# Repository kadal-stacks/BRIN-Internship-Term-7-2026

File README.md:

<!-- Official BRIN logo sourced from Wikimedia Commons; no AI-generated imagery is used. -->
<p align="center">
  
</p>

<h1 align="center">BRIN Internship | Term 7 · 2026</h1>

<p align="center">
  Catatan kerja dan hasil praktik di bidang embedded systems, firmware mikrokontroler, serta desain rangkaian dan PCB.
</p>

<p align="center">

</p>

---

## Tentang repositori

Repositori ini mengumpulkan pekerjaan teknis selama **Magang BRIN Term 7 (2026)**. Isinya berkembang melalui proyek KiCad untuk perancangan elektronik dan PCB, eksperimen program mikrokontroler, serta contoh firmware untuk latihan dan pengujian.

Struktur dibuat mengikuti kelompok pekerjaan agar file desain, source code, dan library pendukung tetap berada dekat dengan proyek masing-masing. Status setiap desain perlu dinilai dari file dan hasil verifikasi yang tersedia; keberadaan file proyek tidak otomatis berarti desain sudah tervalidasi atau siap fabrikasi.

## Ruang lingkup

### 1. Desain elektronik dan PCB dengan KiCad

| Folder | Isi |
| --- | --- |
| [`KiCAD/ATMega16-STM32 BP Adapter`](KiCAD/ATMega16-STM32%20BP%20Adapter) | Proyek adapter/pemetaan koneksi ATmega16 ke board STM32, dengan varian **SMD** dan **THT**. Berisi project, schematic, layout PCB, dan file pendukung yang tersedia. |
| [`KiCAD/Howland-VCCS`](KiCAD/Howland-VCCS) | Proyek rangkaian Howland Voltage-Controlled Current Source menggunakan TL072, dengan beberapa varian footprint/perakitan. |
| [`KiCAD/Impedance-meter2D_Main Board`](KiCAD/Impedance-meter2D_Main%20Board) | Folder proyek untuk main board impedance meter. Kelengkapan desain dapat berbeda dari proyek lainnya. |
| [`KiCAD/Part Lib/Kicad-STM32`](KiCAD/Part%20Lib/Kicad-STM32) | Library simbol, footprint, dan model 3D untuk modul STM32 **Blue Pill** dan **Black Pill**. Lihat README di dalam folder untuk rincian library. |
| [`KiCAD/Folder Tugas`](KiCAD/Folder%20Tugas) | Folder untuk materi/tugas KiCad. |

Format yang umum dijumpai antara lain `.kicad_pro` (project), `.kicad_sch` (schematic), `.kicad_pcb` (PCB layout), `.kicad_sym` (symbol library), dan `.kicad_mod` (footprint).

### 2. Firmware dan eksperimen mikrokontroler

| Lokasi | Isi |
| --- | --- |
| [`Program_MCU/AVR/AVR Atmega 328p - Arduino UNO R3`](Program_MCU/AVR/AVR%20Atmega%20328p%20-%20Arduino%20UNO%20R3) | Eksperimen pada ATmega328P/Arduino Uno R3, termasuk proyek ADC dan program LED non-blocking. |
| [`LED-Berjalan.cpp`](LED-Berjalan.cpp) | Contoh program LED berjalan. |
| [`Non-blocking using Multi LED.cpp`](Non-blocking%20using%20Multi%20LED.cpp) | Contoh pengaturan beberapa pola LED tanpa bergantung pada jeda blocking di loop utama. |

Sebagian proyek firmware memiliki `platformio.ini` dan dapat dibuka sebagai proyek PlatformIO. Untuk source code yang berdiri sendiri, pilih board, framework, pin, serta konfigurasi build yang sesuai sebelum mengompilasi.

## Deliverable PCB dan firmware terbaru

### PCB dengan paket Gerber dan gambar area

| Board | Luas outline | Dokumentasi |
| --- | ---: | --- |
| ATmega16–STM32 Adapter SMD | 1,450.75 mm² (14.5075 cm²) | [Gerber, drill, dan gambar area](KiCAD/ATMega16-STM32%20BP%20Adapter/ATMega16-STM32%20BP%20Adapter_SMD/README.md) |
| Howland VCCS TL072 THT | 3,506.24 mm² (35.0624 cm²) | [Gerber, drill, dan gambar area](KiCAD/Howland-VCCS/Howland-VCCS-TL072/README.md) |
| Howland VCCS TL072 SMD/hybrid | 618.85 mm² (6.1885 cm²) | [Gerber, drill, dan gambar area](KiCAD/Howland-VCCS/Howland-VCCS-TL072_SMD/Howland-VCCS-TL072_SMD/README.md) |

Luas dihitung dari outline `Edge.Cuts` pada file PCB sebagai rounded rectangle, bukan dari perkiraan visual. Board Raspberry Pi Zero Dev Board juga memiliki ukuran outline yang didokumentasikan, tetapi Gerber belum tersedia.

### Firmware AD9833

- [VCCS–AD9833 Frequency Controller (Arduino Nano)](Program_MCU/AVR/AVR%20Atmega%20328p%20-%20Arduino%20Nano/VCCS-AD9833%20Regulator/README.md)
- [Salinan di folder Arduino UNO R3](Program_MCU/AVR/AVR%20Atmega%20328p%20-%20Arduino%20UNO%20R3/VCCS%20-%20AD9833%20Regulator/README.md). Catatan: konfigurasi `platformio.ini` saat ini masih memilih board Nano.

## Alur kerja

Alur berikut merangkum cara menavigasi dan melanjutkan pekerjaan di repositori ini. Langkah verifikasi tetap perlu disesuaikan dengan proyek dan hardware yang digunakan.

1. **Pilih proyek yang relevan.** Buka folder di `KiCAD/` untuk pekerjaan desain atau `Program_MCU/` untuk eksperimen firmware.
2. **Buka file proyek utama.** Untuk KiCad, buka file `.kicad_pro` di folder proyek agar hubungan schematic, PCB, dan library lokal lebih mudah dipertahankan.
3. **Periksa keterkaitan desain.** Pastikan nomor pin, nama net, simbol, footprint, orientasi konektor, ukuran mekanik, dan tegangan logika sesuai datasheet serta modul fisik. Hal ini sangat penting untuk adapter ATmega16–STM32.
4. **Verifikasi sebelum menganggap selesai.** Tinjau Electrical Rules Checker (ERC) untuk schematic dan Design Rules Checker (DRC) untuk PCB. Periksa hasil simulasi atau pengujian firmware jika tersedia. ERC/DRC yang bersih sendiri tidak menjamin rangkaian bekerja pada hardware.
5. **Simpan perubahan secara terstruktur.** Pertahankan file yang dibutuhkan proyek, hindari memasukkan file lock atau file sementara editor, lalu commit perubahan dengan pesan yang menjelaskan lingkup pekerjaan.

## Referensi visual

Gambar di bawah merupakan tangkapan layar asli dari dokumentasi KiCad, digunakan sebagai referensi antarmuka schematic dan PCB editor, bukan sebagai klaim bahwa gambar tersebut adalah hasil desain proyek ini.

<p align="center">

</p>

## Galeri perangkat keras: foto referensi non-AI

Foto berikut berasal dari halaman produk/vendor atau aset foto yang sudah tersimpan di repository. Gambar membantu mengenali komponen, **bukan bukti bahwa board pada proyek ini sudah dirakit atau diuji**.

<p align="center">

</p>

<sub>Sumber foto: <a href="https://www.mikroe.com/atmega16">MikroE ATmega16</a>, aset <a href="KiCAD/Part%20Lib/Kicad-STM32/README.md">Blue Pill repository</a>, <a href="https://www.ti.com/product/TL072">TI TL072 / foto paket IC dari pemasok</a>, <a href="https://wholesale.pimoroni.com/en-eu/products/adafruit-bmp280-i2c-or-spi-barometric-pressure-altitude-sensor">modul BMP280 dari pemasok</a>, dan <a href="https://laelectronica.com.gt/arduino-uno-rev3">foto Arduino Uno R3</a>. Foto TL072 yang ditampilkan adalah paket DIP-8; periksa footprint proyek sebelum membeli komponen.</sub>

## Memulai

- **KiCad:** instal KiCad, lalu buka file `.kicad_pro` dari folder proyek yang akan dikerjakan.
- **Firmware:** untuk proyek yang memiliki `platformio.ini`, gunakan VS Code dengan ekstensi PlatformIO atau PlatformIO CLI. Pastikan board/framework cocok dengan konfigurasi proyek.
- **Hardware:** sebelum upload firmware atau memberi daya, cocokkan wiring dan level tegangan dengan datasheet serta lakukan pemeriksaan dasar untuk menghindari kerusakan komponen.

## Catatan status dan akurasi

Repositori ini merupakan arsip kerja yang berkembang. Skema, mapping pin, footprint, routing, pengaturan panel, dan source code perlu diverifikasi terhadap versi tool, datasheet komponen, hardware aktual, serta persyaratan manufaktur. Jangan menganggap desain siap produksi hanya berdasarkan visual layout atau status file yang sudah di-commit.

## Sumber gambar dan aset

- **Logo BRIN:** karya resmi Badan Riset dan Inovasi Nasional; ditautkan dari [Wikimedia Commons](https://commons.wikimedia.org/wiki/File:LOGO_BRIN_NEW.jpg), yang mencatat sumber dan status domain publik di Indonesia.
- **Tangkapan layar KiCad:** [KiCad 8 release article](https://www.kicad.org/blog/2024/02/Version-8.0.0-Released/) dan [dokumentasi PCB Editor KiCad](https://docs.kicad.org/9.0/it/pcbnew/pcbnew.html).
- **Library STM32:** lihat [README library lokal](KiCAD/Part%20Lib/Kicad-STM32/README.md) untuk detail simbol, footprint, model 3D, dan konteks sumbernya.

<p align="center">
  <sub>Logo BRIN digunakan untuk menunjukkan konteks kegiatan magang. Repositori ini tidak menyatakan dirinya sebagai repositori resmi BRIN.</sub>
</p>

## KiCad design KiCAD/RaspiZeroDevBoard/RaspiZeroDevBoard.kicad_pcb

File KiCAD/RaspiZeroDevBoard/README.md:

<p align="center">
  
</p>

# Raspberry Pi Zero Dev Board

Carrier/development board untuk Raspberry Pi Zero dengan interface tambahan untuk akuisisi analog, komunikasi, RTC, display, dan distribusi daya.

## Preview area board

| Parameter | Nilai |
| --- | ---: |
| Lebar outline | 120.65 mm |
| Tinggi outline | 162.56 mm |
| Radius sudut | 6 mm |
| Luas bounding rectangle | 19,612.86 mm² |
| Koreksi empat sudut rounded | 30.90 mm² |
| **Luas bidang PCB aktual** | **19,581.96 mm²** |
| **Konversi** | **195.8196 cm²** |

Luas dihitung dari rounded-rectangle pada layer `Edge.Cuts` file `RaspiZeroDevBoard.kicad_pcb`:

`A = W × H − (4 − π)r²`

SVG adalah gambar ukur/preview vektor yang dibuat dari geometri CAD. Ini bukan foto produk, bukan render AI, dan bukan plot Gerber.

## Fungsi board

Schematic menunjukkan carrier board Raspberry Pi Zero dengan sejumlah interface eksternal:

| Blok | Komponen/label pada schematic | Fungsi yang dituju |
| --- | --- | --- |
| Host | J1, footprint Raspberry Pi Zero socketed | Koneksi modul Raspberry Pi Zero |
| ADC | U2 ADS1115, input ADC_Input0–ADC_Input3, R/C bertanda ADC_R/ADC_C | Empat kanal input analog melalui ADC eksternal |
| RTC | A2, Module_ZS-042 | Modul RTC DS3231 |
| RS-485 | U1, TLL_TO_RS-485 / module MAX485 | Interface komunikasi RS-485 |
| Display | A1, I2C-LCD1602 | Display karakter 16×2 melalui I²C |
| DC-DC | PS1, LM2596_Module | Modul regulator DC-DC |
| Serial/peripheral | Header UART, SPI, I²C | Akses interface peripheral |
| Power | Power_In, 5V Out, 3V3 Out | Input dan distribusi rail daya |
| User I/O | Tombol SW1/SW2, LED D1/D2, solder jumper | Kontrol lokal, indikator, dan konfigurasi board |

Schematic juga menunjukkan solder-jumper untuk pemilihan alamat ADS1115 (0x49, 0x4A, 0x4B), enable LED, enable button, RTC interrupt/SQW, dan arah RS-485. Nilai komponen bertanda generik seperti `ADC_R`, `ADC_C`, `I2C_R`, dan `R_LED` perlu diselesaikan pada BOM sebelum produksi.

## Catatan desain yang perlu diverifikasi

- Symbol J1 bernilai `Raspberry_Pi_4`, sedangkan footprint-nya bernama Raspberry Pi Zero. Pastikan symbol/value hanya label yang belum diperbarui atau memang perlu dikoreksi.
- Cek kebutuhan catu daya Raspberry Pi, distribusi 5V/3V3, rating modul LM2596, dan koneksi ground.
- Periksa mapping pin GPIO/peripheral Pi Zero terhadap header UART, SPI, I²C, ADC, dan RS-485.
- Pastikan resistansi pembagi/filter pada input ADS1115 dan rentang tegangan analog aman untuk input ADC.
- Pastikan konfigurasi jumper alamat ADS1115 tidak bertabrakan dan pull-up I²C sesuai bus.

## Status manufaktur

File project, schematic, dan PCB tersedia. Namun folder ini **belum berisi paket Gerber, file drill, atau screenshot area board asli**. SVG di atas hanya preview geometri dan perhitungan luas. Sebelum fabrikasi, jalankan ERC/DRC pada revisi terkini, plot seluruh layer Gerber, generate PTH/NPTH drill, lalu periksa hasilnya.

## File utama

- `RaspiZeroDevBoard.kicad_pro`
- `RaspiZeroDevBoard.kicad_sch`
- `RaspiZeroDevBoard.kicad_pcb`
- `RaspiZeroDevBoard PCB Area.svg`

---

[README KiCad](../README.md)

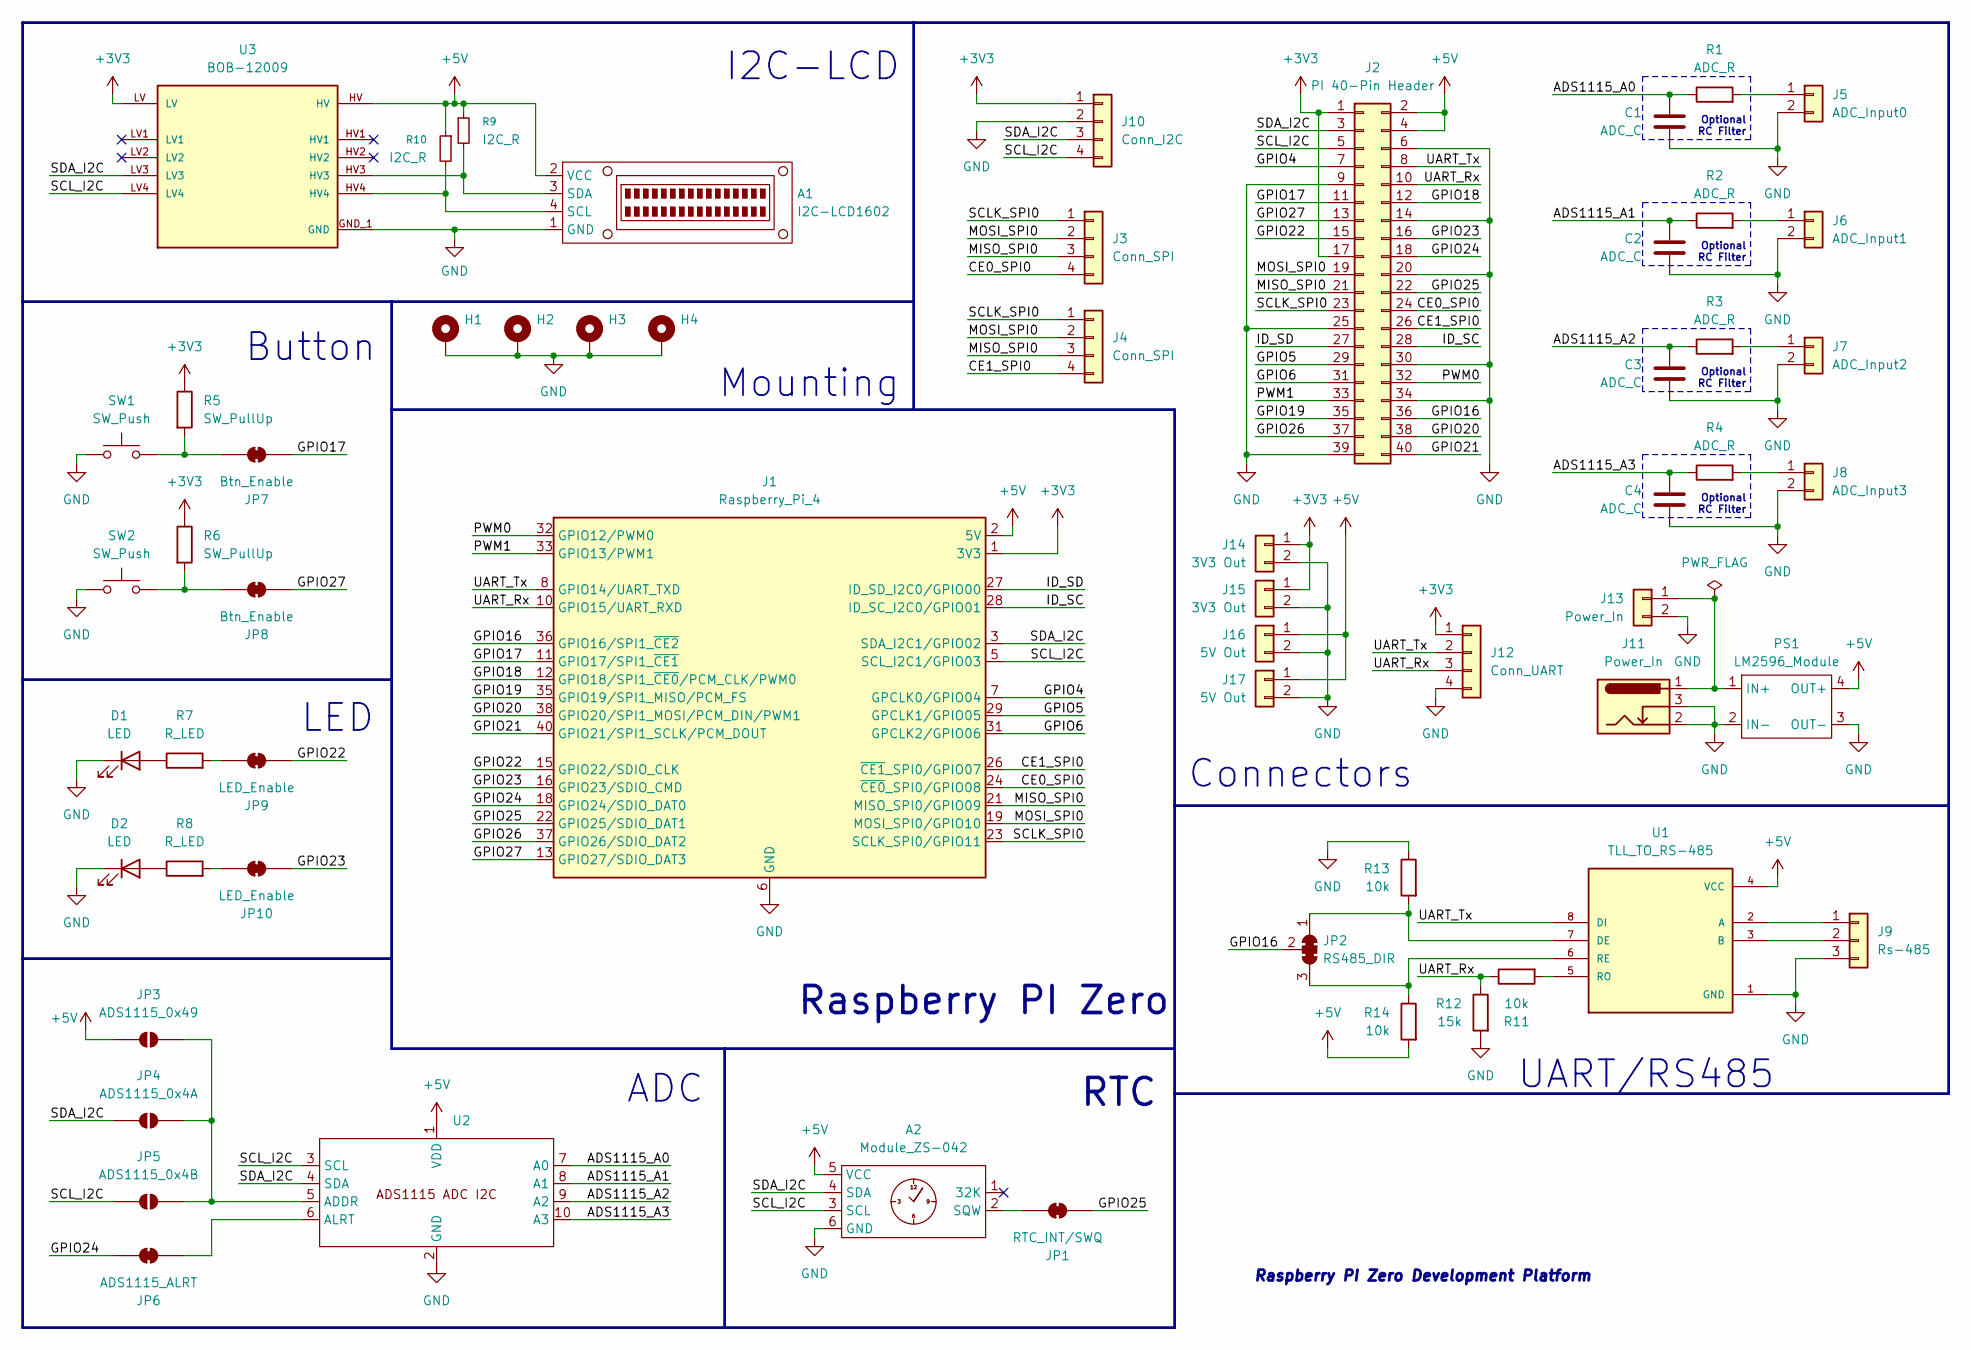
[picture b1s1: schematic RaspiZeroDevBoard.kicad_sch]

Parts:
A1: I2C-LCD1602; MODULE_LCD-16X2
A2: Module_ZS-042; MODULE_DS3231
C1, C2, C3, C4: ADC_C; C_0603_1608Metric
D1, D2: LED; LED_D5.0mm
H1, H2, H3, H4: MountingHole_Pad; MountingHole_2.2mm_M2
J1: Raspberry_Pi_4; Raspberry_Pi_Zero_Socketed_THT_FaceDown_MountingHoles
J2: PI 40-Pin Header; PinHeader_2x20_P2.54mm_Vertical
J3, J4: Conn_SPI; Molex_KK-254_AE-6410-04A_1x04_P2.54mm_Vertical
J5: ADC_Input0; Molex_KK-254_AE-6410-02A_1x02_P2.54mm_Vertical
J6: ADC_Input1; Molex_KK-254_AE-6410-02A_1x02_P2.54mm_Vertical
J7: ADC_Input2; Molex_KK-254_AE-6410-02A_1x02_P2.54mm_Vertical
J8: ADC_Input3; Molex_KK-254_AE-6410-02A_1x02_P2.54mm_Vertical
J9: Rs-485; Molex_KK-254_AE-6410-03A_1x03_P2.54mm_Vertical
J10: Conn_I2C; Molex_KK-254_AE-6410-04A_1x04_P2.54mm_Vertical
J11: Power_In; BarrelJack_Horizontal
J12: Conn_UART; Molex_KK-254_AE-6410-04A_1x04_P2.54mm_Vertical
J13: Power_In; Molex_KK-254_AE-6410-02A_1x02_P2.54mm_Vertical
J14, J15: 3V3 Out; Molex_KK-254_AE-6410-02A_1x02_P2.54mm_Vertical
J16, J17: 5V Out; Molex_KK-254_AE-6410-02A_1x02_P2.54mm_Vertical
JP1: RTC_INT/SWQ; SolderJumper-2_P1.3mm_Bridged_RoundedPad1.0x1.5mm
JP2: RS485_DIR; SolderJumper-3_P1.3mm_Bridged123_RoundedPad1.0x1.5mm
JP3: ADS1115_0x49; SolderJumper-2_P1.3mm_Open_RoundedPad1.0x1.5mm
JP4: ADS1115_0x4A; SolderJumper-2_P1.3mm_Open_RoundedPad1.0x1.5mm
JP5: ADS1115_0x4B; SolderJumper-2_P1.3mm_Open_RoundedPad1.0x1.5mm
JP6: ADS1115_ALRT; SolderJumper-2_P1.3mm_Bridged_RoundedPad1.0x1.5mm
JP7, JP8: Btn_Enable; SolderJumper-2_P1.3mm_Bridged_RoundedPad1.0x1.5mm
JP9, JP10: LED_Enable; SolderJumper-2_P1.3mm_Bridged_RoundedPad1.0x1.5mm
PS1: LM2596_Module; LM2596-DC-DC
R1, R2, R3, R4: ADC_R; R_0603_1608Metric
R5, R6: SW_PullUp; R_0603_1608Metric
R7, R8: R_LED; R_0603_1608Metric
R9, R10: I2C_R; R_0603_1608Metric
R11, R13, R14: 10k; R_0603_1608Metric
R12: 15k; R_0603_1608Metric
SW1, SW2: SW_Push; SW_PUSH_6mm_H5mm
U1: TLL_TO_RS-485; MODULE_MAX485_MODULE_5V_LOGIC_TLL_TO_RS-485_CONVERTER; PARTREV 1r0
U2: Modul_ADS1115_ADC_I2C
U3: BOB-12009; CONV_BOB-12009; PARTREV 01

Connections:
+3V3: J1.1 (3V3), J1.17 (3V3), J2.1, J2.17, J10.1, J12.1, J14.1, J15.1, R5.1, R6.1, U3.LV
+5V: A1.2 (VCC), A2.5 (VCC), J1.2 (5V), J1.4 (5V), J2.2, J2.4, J16.1, J17.1, JP3.1 (A), PS1.4 (OUT+), R9.1, R10.1, R14.2, U1.4 (VCC), U2.1 (VDD), U3.HV
/ADS1115_A0: C1.1, R1.1, U2.7 (A0)
/ADS1115_A1: C2.1, R2.1, U2.8 (A1)
/ADS1115_A2: C3.1, R3.1, U2.9 (A2)
/ADS1115_A3: C4.1, R4.1, U2.10 (A3)
/CE0_SPI0: J1.24 (~CE0_SPI0/GPIO08), J2.24, J3.4
/CE1_SPI0: J1.26 (~CE1_SPI0/GPIO07), J2.26, J4.4
/GPIO4: J1.7 (GPCLK0/GPIO04), J2.7
/GPIO5: J1.29 (GPCLK1/GPIO05), J2.29
/GPIO6: J1.31 (GPCLK2/GPIO06), J2.31
/GPIO16: J1.36 (GPIO16/SPI1_~CE2), J2.36, JP2.2 (C)
/GPIO17: J1.11 (GPIO17/SPI1_~CE1), J2.11, JP7.2 (B)
/GPIO18: J1.12 (GPIO18/SPI1_~CE0/PCM_CLK/PWM0), J2.12
/GPIO19: J1.35 (GPIO19/SPI1_MISO/PCM_FS), J2.35
/GPIO20: J1.38 (GPIO20/SPI1_MOSI/PCM_DIN/PWM1), J2.38
/GPIO21: J1.40 (GPIO21/SPI1_SCLK/PCM_DOUT), J2.40
/GPIO22: J1.15 (GPIO22/SDIO_CLK), J2.15, JP9.2 (B)
/GPIO23: J1.16 (GPIO23/SDIO_CMD), J2.16, JP10.2 (B)
/GPIO24: J1.18 (GPIO24/SDIO_DAT0), J2.18, JP6.1 (A)
/GPIO25: J1.22 (GPIO25/SDIO_DAT1), J2.22, JP1.2 (B)
/GPIO26: J1.37 (GPIO26/SDIO_DAT2), J2.37
/GPIO27: J1.13 (GPIO27/SDIO_DAT3), J2.13, JP8.2 (B)
/ID_SC: J1.28 (ID_SC_I2C0/GPIO01), J2.28
/ID_SD: J1.27 (ID_SD_I2C0/GPIO00), J2.27
/MISO_SPI0: J1.21 (MISO_SPI0/GPIO09), J2.21, J3.3, J4.3
/MOSI_SPI0: J1.19 (MOSI_SPI0/GPIO10), J2.19, J3.2, J4.2
/PWM0: J1.32 (GPIO12/PWM0), J2.32
/PWM1: J1.33 (GPIO13/PWM1), J2.33
/SCLK_SPI0: J1.23 (SCLK_SPI0/GPIO11), J2.23, J3.1, J4.1
/SCL_I2C: A2.3 (SCL), J1.5 (SCL_I2C1/GPIO03), J2.5, J10.4, JP5.1 (A), U2.3 (SCL), U3.LV4
/SDA_I2C: A2.4 (SDA), J1.3 (SDA_I2C1/GPIO02), J2.3, J10.3, JP4.1 (A), U2.4 (SDA), U3.LV3
/UART_Rx: J1.10 (GPIO15/UART_RXD), J2.10, J12.3, R11.1, R12.1
/UART_Tx: J1.8 (GPIO14/UART_TXD), J2.8, J12.2, U1.8 (DI)
GND: A1.1 (GND), A2.6 (GND), C1.2, C2.2, C3.2, C4.2, D1.1 (K), D2.1 (K), H1.1, H2.1, H3.1, H4.1, J1.6 (GND), J1.9 (GND), J1.14 (GND), J1.20 (GND), J1.25 (GND), J1.30 (GND), J1.34 (GND), J1.39 (GND), J2.6, J2.9, J2.14, J2.20, J2.25, J2.30, J2.34, J2.39, J5.2, J6.2, J7.2, J8.2, J9.3, J10.2, J11.2, J11.3, J12.4, J13.2, J14.2, J15.2, J16.2, J17.2, PS1.2 (IN-), PS1.3 (OUT-), R12.2, R13.1, SW1.1, SW2.1, U1.1 (GND), U2.2 (GND), U3.GND_1 (GND), U3.GND_2 (GND)
unnamed: A1.4 (SCL), R10.2, U3.HV4
unnamed: A1.3 (SDA), R9.2, U3.HV3
unnamed: A2.2 (SQW), JP1.1 (A)
unnamed: D1.2 (A), R7.1
unnamed: D2.2 (A), R8.1
unnamed: J5.1, R1.2
unnamed: J6.1, R2.2
unnamed: J7.1, R3.2
unnamed: J8.1, R4.2
unnamed: J9.1, U1.2 (A)
unnamed: J9.2, U1.3 (B)
unnamed: J11.1, J13.1, PS1.1 (IN+)
unnamed: JP2.1 (A), R13.2, U1.7 (DE)
unnamed: JP2.3 (B), R14.1, U1.6 (RE)
unnamed: JP3.2 (B), JP4.2 (B), JP5.2 (B), U2.5 (ADDR)
unnamed: JP6.2 (B), U2.6 (ALRT)
unnamed: JP7.1 (A), R5.2, SW1.2
unnamed: JP8.1 (A), R6.2, SW2.2
unnamed: JP9.1 (A), R7.2
unnamed: JP10.1 (A), R8.2
unnamed: R11.2, U1.5 (RO)

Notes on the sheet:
ADC
Optional RC Filter
RTC
Mounting
Raspberry PI Zero
Raspberry PI Zero Development Platform
Connectors
LED
Button
UART/RS485
I2C-LCD

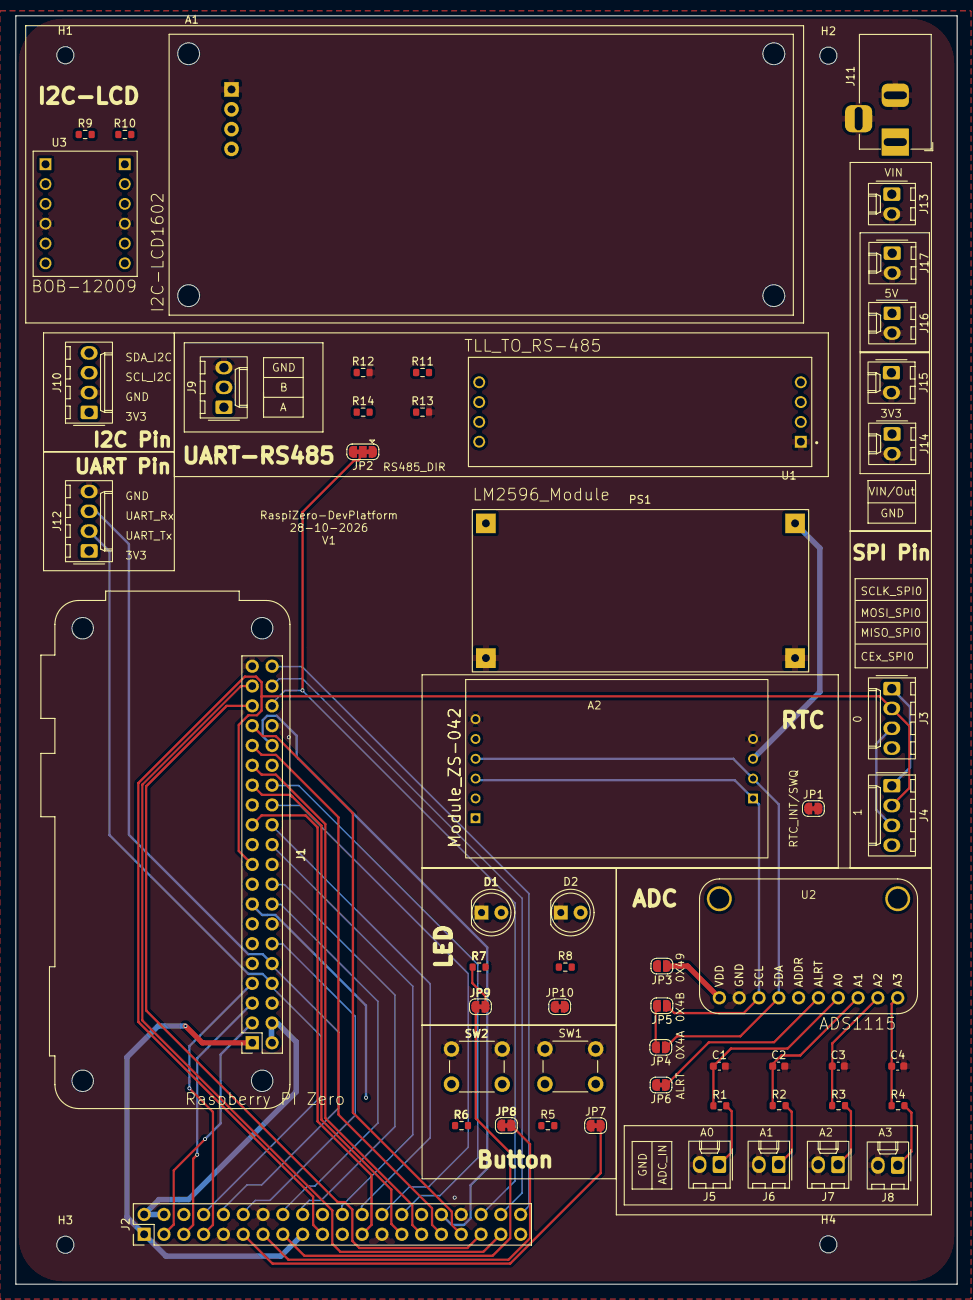
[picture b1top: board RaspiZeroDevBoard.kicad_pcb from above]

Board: 2 copper layers, 120.6 x 162.6 mm, 59 parts (0 on the bottom side), 56 nets.

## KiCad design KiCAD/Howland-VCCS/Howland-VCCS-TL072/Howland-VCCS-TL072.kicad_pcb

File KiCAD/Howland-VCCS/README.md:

<p align="center">
  
</p>

# Howland Voltage-Controlled Current Source (VCCS)

Folder ini berisi dua varian manufaktur aktif dari Howland current pump berbasis op-amp TL072, serta workspace buffer yang masih terpisah.

Topologi Howland menggunakan op-amp dan jaringan resistor umpan balik untuk mengubah tegangan kendali menjadi arus pada beban. Kinerja bergantung pada rasio/matching resistor, supply op-amp, rentang output, beban, serta compliance voltage.

## Varian dengan paket Gerber

| Varian | Folder proyek | Area board | Paket |
| --- | --- | ---: | --- |
| THT | [Howland-VCCS-TL072](Howland-VCCS-TL072/README.md) | **3,506.24 mm² / 35.0624 cm²** | [Gerber ZIP](Howland-VCCS-TL072/Howland-VCCS-TL072-Gerber.zip) |
| SMD/hybrid | [Howland-VCCS-TL072_SMD](Howland-VCCS-TL072_SMD/Howland-VCCS-TL072_SMD/README.md) | **618.85 mm² / 6.1885 cm²** | [Gerber ZIP](Howland-VCCS-TL072_SMD/Howland-VCCS-TL072_SMD/Howland-VCCS-TL072-SMD-Gerber.zip) |

## Ringkasan komponen schematic terbaru

### THT

| Komponen | Jumlah / nilai |
| --- | ---: |
| U1 TL072, DIP-8 | 1 |
| R1–R4 | 100 kΩ, 4 buah |
| R5 | 150 Ω |
| RV1 | 1 kΩ, trimmer THT |
| J1–J2 | Header 1×3 |
| H1–H4 | Mounting hole M2.2 |

### SMD/hybrid

| Komponen | Jumlah / nilai |
| --- | ---: |
| U1 TL072, DIP-8 (THT) | 1 |
| R1–R4, SMD 0805 | 100 kΩ, 4 buah |
| R5, SMD 0805 | 150 Ω |
| RV1 | 1 kΩ, trimmer THT |
| J4 | Header 1×6 |
| H1–H2 | Mounting hole M2.2 |

Varian SMD adalah hybrid, bukan full-SMD: schematic terbaru masih menetapkan TL072 footprint DIP-8 dan trimmer THT. Rujuk README proyek untuk rincian layer Gerber, area, dan gambar board.

## Workspace lain

Workspace [VCCS 2 Buffer](VCCS%202%20Buffer/README.md) tetap terpisah. Schematic menampilkan AD826ANZ, dua TL082, dan resistor yang masih memakai value generik `R_Small`. File PCB saat ini masih berupa stub KiCad tanpa outline maupun layout, sehingga luas board dan paket Gerber belum tersedia.

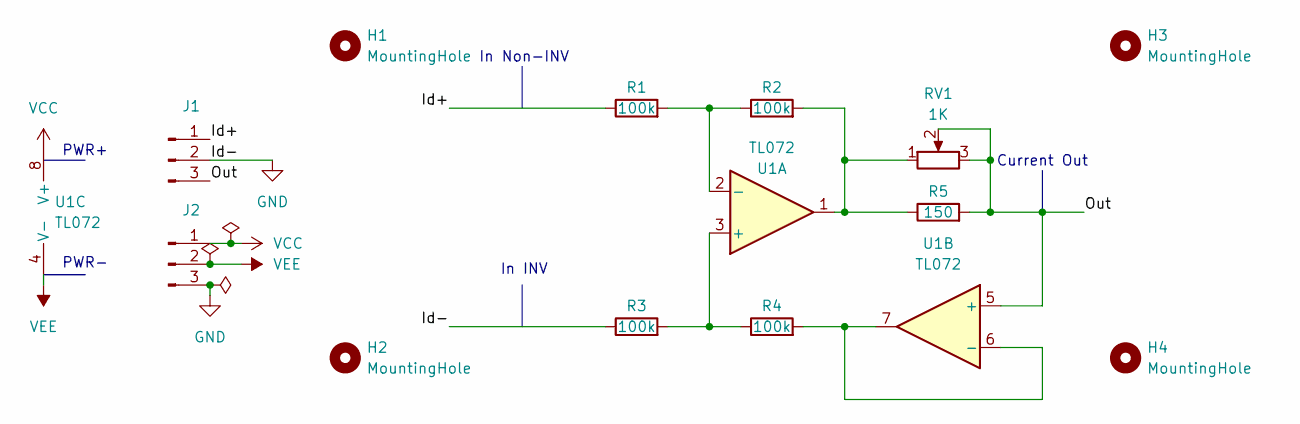
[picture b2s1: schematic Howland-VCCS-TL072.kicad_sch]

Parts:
H1, H2, H3, H4: MountingHole; MountingHole_2.2mm_M2
J1, J2: Conn_01x03_Pin; PinHeader_1x03_P2.54mm_Vertical
R1, R2, R3, R4: 100k; R_Axial_DIN0207_L6.3mm_D2.5mm_P10.16mm_Horizontal
R5: 150; R_Axial_DIN0207_L6.3mm_D2.5mm_P10.16mm_Horizontal
RV1: 1K; Potentiometer_Bourns_3296W_Vertical
U1: TL072; DIP-8_W7.62mm

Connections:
/Id+: J1.1, R1.1
/Out: J1.3, R5.2, RV1.2, RV1.3, U1.5 (+)
GND: J1.2, J2.3, R3.1
unnamed: R2.2, R5.1, RV1.1, U1.1
unnamed: R3.2, R4.1, U1.3 (+)
unnamed: R1.2, R2.1, U1.2 (-)
unnamed: R4.2, U1.6 (-), U1.7
VCC: J2.1, U1.8 (V+)
VEE: J2.2, U1.4 (V-)

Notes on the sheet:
PWR+
PWR-
In Non-INV
In INV
Current Out

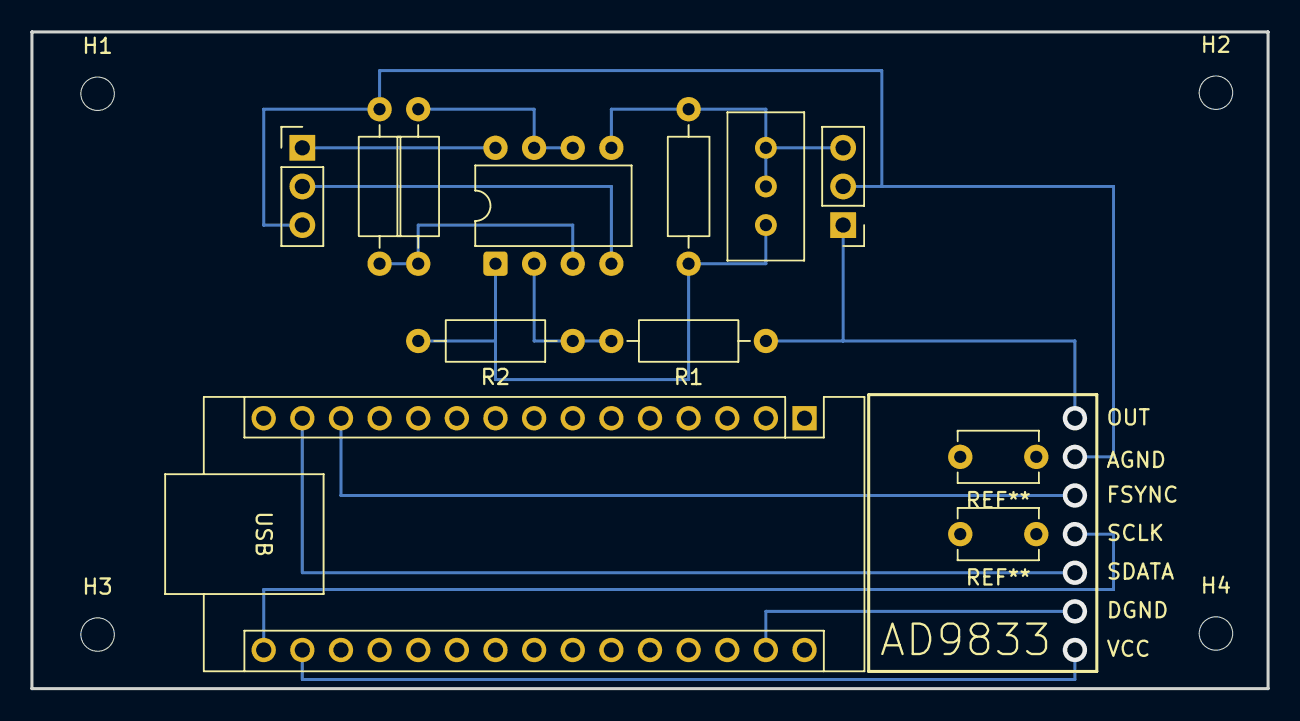
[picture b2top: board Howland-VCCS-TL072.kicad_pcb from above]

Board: 2 copper layers, 81.3 x 43.2 mm, 14 parts (0 on the bottom side), 9 nets.

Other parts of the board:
A1: Arduino_Nano_v3.x; Arduino_Nano

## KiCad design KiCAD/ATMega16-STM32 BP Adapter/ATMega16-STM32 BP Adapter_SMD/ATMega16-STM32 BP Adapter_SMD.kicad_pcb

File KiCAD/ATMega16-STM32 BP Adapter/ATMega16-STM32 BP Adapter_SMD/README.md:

<table align="center">
  <tr>
    <td align="center" valign="middle" width="33%">
      
    </td>
    <td align="center" valign="middle" width="33%">
      
    </td>
    <td align="center" valign="middle" width="33%">
      
    </td>
  </tr>
</table>
<p align="center"><sub>STM32 Blue Pill reference · STM32F103C8T6 · Arm® Cortex®-M3 core</sub></p>

# ATmega16–STM32 Adapter (SMD)

Varian SMD dari adapter breakout ATmega16–STM32. README ini merangkum mapping dari workbook, file manufaktur yang sudah di-commit, dan dimensi area board yang dihitung dari outline PCB.

## Preview board dan luas area

| Parameter | Nilai |
| --- | ---: |
| Lebar bounding outline | 25.40 mm |
| Tinggi bounding outline | 57.15 mm |
| Radius sudut | 1.00 mm |
| Luas bounding rectangle | 1,451.61 mm² |
| Koreksi empat sudut membulat | 0.86 mm² |
| **Luas bidang PCB aktual** | **1,450.75 mm²** |
| **Konversi** | **14.5075 cm²** |

Perhitungan memakai geometri rounded rectangle dari `Edge.Cuts` pada file PCB/Gerber: `A = W × H − (4 − π)r²`. Nilai area tidak memasukkan area luar board atau clearance manufaktur.

## Fungsi board dan komponen

Board ini merutekan sinyal antar-header ATmega16 dan sisi konektor STM32 Blue Pill. Schematic SMD menunjukkan:

| Ref. | Komponen | Fungsi |
| --- | --- | --- |
| J1, J2 | Socket 1×20, pitch 2.54 mm | Konektor socket pada salah satu sisi antarmuka |
| J3, J4 | Pin header 1×20, pitch 2.54 mm | Konektor header pada sisi lainnya |
| Net labels | ATM16.PA/PB/PC/PD, RESET, dan label periferal | Memberi identitas jalur sinyal |
| Power symbols | 3V3, 5V/VCC, GND, PWR_FLAG | Penamaan rail dan pemeriksaan ERC |

Tidak ada IC level-shifter aktif yang terlihat pada schematic ini. Board adalah adapter routing, bukan rangkaian pengubah level. Verifikasi toleransi setiap pin STM32 terhadap sinyal ATmega16 sebelum koneksi langsung.

## Pin mapping dari workbook

Tabel berikut mempertahankan pemetaan yang dicatat dalam workbook **ATmega16-STM32-Mapping.xlsx**, sheet “Routing dan Sinkronisasi Fungsi Pin”. Tujuan pin dan alternate function tetap harus divalidasi terhadap MCU/board aktual dan firmware yang digunakan.

| Pin ATmega16 (DIP-40) | Sinyal/fungsi ATmega16 | Tujuan STM32 | Fungsi STM32 / catatan |
| ---: | --- | --- | --- |
| 40–33 | PA0–PA7 / ADC0–ADC7 | PA0–PA7 | Input analog |
| 14 | PD0 / RXD | PA10 | USART1_RX |
| 15 | PD1 / TXD | PA9 | USART1_TX |
| 5 | PB4 / SS | PB12 | SPI2_NSS, chip select |
| 6 | PB5 / MOSI | PB15 | SPI2_MOSI |
| 7 | PB6 / MISO | PB14 | SPI2_MISO |
| 8 | PB7 / SCK | PB13 | SPI2_SCK |
| 22 | PC0 / SCL | PB6 | I2C1_SCL |
| 23 | PC1 / SDA | PB7 | I2C1_SDA |
| 16 | PD2 / INT0 | PB8 | GPIO + EXTI |
| 17 | PD3 / INT1 | PB9 | GPIO + EXTI |
| 18 | PD4 / OC1B | PA8 | TIM1_CH1 |
| 19 | PD5 / OC1A | PB0 | TIM3_CH3 |
| 20 | PD6 / ICP1 | PB1 | TIM3_CH4 |
| 21 | PD7 / OC2 | PB4 | TIM3_CH1 |
| 1 | PB0 / XCK-T0 | PB10 | TIM2_CH3 menurut workbook |
| 2 | PB1 / T1 | PA14 (tertulis di workbook) | **Perlu koreksi:** PA14 adalah JTCK/SWCLK pada STM32F103; jangan anggap sebagai TIM1_ETR. Verifikasi pin timer yang benar sebelum memakai fungsi ini. |
| 3 | PB2 / INT2-AIN0 | PB2 | GPIO + EXTI2; workbook mencatat cek BOOT1 strap |
| 4 | PB3 / OC0-AIN1 | PB3 | TIM2_CH2; workbook mencatat perlu remapping |
| 9 | RESET | RESET | Hardware reset |
| 10 | VCC | 5V+ | Sumber daya menurut workbook; verifikasi rancangan power aktual |
| 11 | GND | GND | Ground |
| 12 | XTAL2 | NC | Gunakan clock onboard Blue Pill menurut workbook |
| 13 | XTAL1 | NC | Gunakan clock onboard Blue Pill menurut workbook |
| 30 | AVCC | NC (tertulis di workbook) | **Perlu review:** datasheet ATmega16 mensyaratkan AVCC terhubung ke VCC, meskipun ADC tidak digunakan |
| 32 | AREF | NC | Tidak diberi pin AREF terpisah pada tabel sisi STM32 |
| 24 | PC2 / TCK | NC | Workbook mencatat sebagai pin khusus/debug |
| 25 | PC3 / TMS | NC | Workbook mencatat sebagai pin khusus/debug |
| 26 | PC4 / TDO | NC | JTAG AVR / GPIO sesuai konfigurasi |
| 27 | PC5 / TDI | NC | Periksa label/fungsi terhadap datasheet |
| 28 | PC6 / TOSC1 | PC14 / OSC32_IN | Muncul pada tabel referensi tambahan, bukan tabel routing utama |
| 29 | PC7 / TOSC2 | PC15 / OSC32_OUT | Muncul pada tabel referensi tambahan, bukan tabel routing utama |
| 31 | GND | GND | Pin GND kedua pada pinout ATmega16 DIP-40 |

### Catatan review elektrik

1. **AVCC:** workbook menandai AVCC sebagai NC. Datasheet Microchip menyatakan AVCC harus dihubungkan ke VCC walaupun ADC tidak digunakan; bila ADC dipakai, ikuti rekomendasi filter yang sesuai. Periksa net PCB sebelum fabrikasi.
2. **PA14:** workbook menuliskan PB1/T1 → PA14/TIM1_ETR. PA14 adalah JTCK/SWCLK pada STM32F103; mapping alternate function tersebut perlu ditinjau dan dikoreksi.
3. **GND pin 31:** pastikan kedua pin GND ATmega16 (pin 11 dan 31) ditangani pada koneksi board.
4. **Level tegangan:** jangan anggap semua input STM32 toleran terhadap 5 V. Schematic tidak memperlihatkan level-shifter aktif.
5. **Pin khusus:** cek BOOT1/PB2, remapping TIM2/PB3, dan konflik pin debug sebelum menetapkan firmware.

Referensi: [datasheet ATmega16 Microchip](https://www.microchip.com/content/dam/mchp/documents/OTH/ProductDocuments/DataSheets/doc2466.pdf), [datasheet STM32F103 ST](https://www.st.com/resource/en/datasheet/cd00210843.pdf).

## Paket Gerber dan drill

**Status: Gerber dan drill tersedia.**

Arsip ZIP di repository bernama **`ATMega16-STM32 BP Adapter_SMD_Geber.zip`** (ejaan “Geber” mengikuti nama file yang sudah ada di GitHub).

[Unduh arsip Gerber](ATMega16-STM32%20BP%20Adapter_SMD_Geber.zip)

Layer individual yang tersedia:

| Layer / file | Isi |
| --- | --- |
| [F_Cu](ATMega16-STM32%20BP%20Adapter_SMD-F_Cu.gbr) | Front copper |
| [B_Cu](ATMega16-STM32%20BP%20Adapter_SMD-B_Cu.gbr) | Back copper |
| [F_Mask](ATMega16-STM32%20BP%20Adapter_SMD-F_Mask.gbr), [B_Mask](ATMega16-STM32%20BP%20Adapter_SMD-B_Mask.gbr) | Solder mask |
| [F_Paste](ATMega16-STM32%20BP%20Adapter_SMD-F_Paste.gbr), [B_Paste](ATMega16-STM32%20BP%20Adapter_SMD-B_Paste.gbr) | Paste |
| [F_Silkscreen](ATMega16-STM32%20BP%20Adapter_SMD-F_Silkscreen.gbr), [B_Silkscreen](ATMega16-STM32%20BP%20Adapter_SMD-B_Silkscreen.gbr) | Silkscreen |
| [Edge_Cuts](ATMega16-STM32%20BP%20Adapter_SMD-Edge_Cuts.gbr) | Board outline / profile |
| [PTH drill](ATMega16-STM32%20BP%20Adapter_SMD-PTH.drl), [NPTH drill](ATMega16-STM32%20BP%20Adapter_SMD-NPTH.drl) | Data pengeboran |
| [Job file](ATMega16-STM32%20BP%20Adapter_SMD-job.gbrjob) | Metadata job Gerber |

Gerber individual dihasilkan dengan KiCad 10.0.5. Cocokkan file dari satu paket/revisi yang sama ketika dikirim ke manufaktur.

## Status pemeriksaan PCB

Laporan DRC yang diberikan sebelumnya mencatat 102 warning yang seluruhnya berhubungan dengan silkscreen: 48 `silk_overlap` dan 54 `silk_over_copper`, dengan 0 unconnected pads dan 0 footprint errors. ERC dinyatakan aman berdasarkan konfirmasi pemilik desain.

**Catatan versi:** laporan tersebut berasal dari pemeriksaan sebelumnya (22 Oktober 2026), sedangkan PCB dan Gerber yang sekarang ada di repository diperbarui pada 12 November 2026. Karena itu, angka warning lama tidak boleh dianggap sebagai hasil DRC untuk revisi Gerber terbaru. Jalankan ERC/DRC ulang pada revisi PCB yang akan diproduksi; isu silkscreen lama tetap relevan sebagai item yang perlu dicek, tetapi statusnya belum terkonfirmasi untuk revisi terbaru.

## File project

- `ATMega16-STM32 BP Adapter_SMD.kicad_pro`: project.
- `ATMega16-STM32 BP Adapter_SMD.kicad_sch`: schematic/net mapping.
- `ATMega16-STM32 BP Adapter_SMD.kicad_pcb`: PCB layout.
- `ATMega16-STM32 BP Adapter_SMD.csv`: data pendamping.
- `fp-lib-table`: konfigurasi footprint library.

---

[README adapter (parent)](../README.md) · [README KiCad](../../README.md)

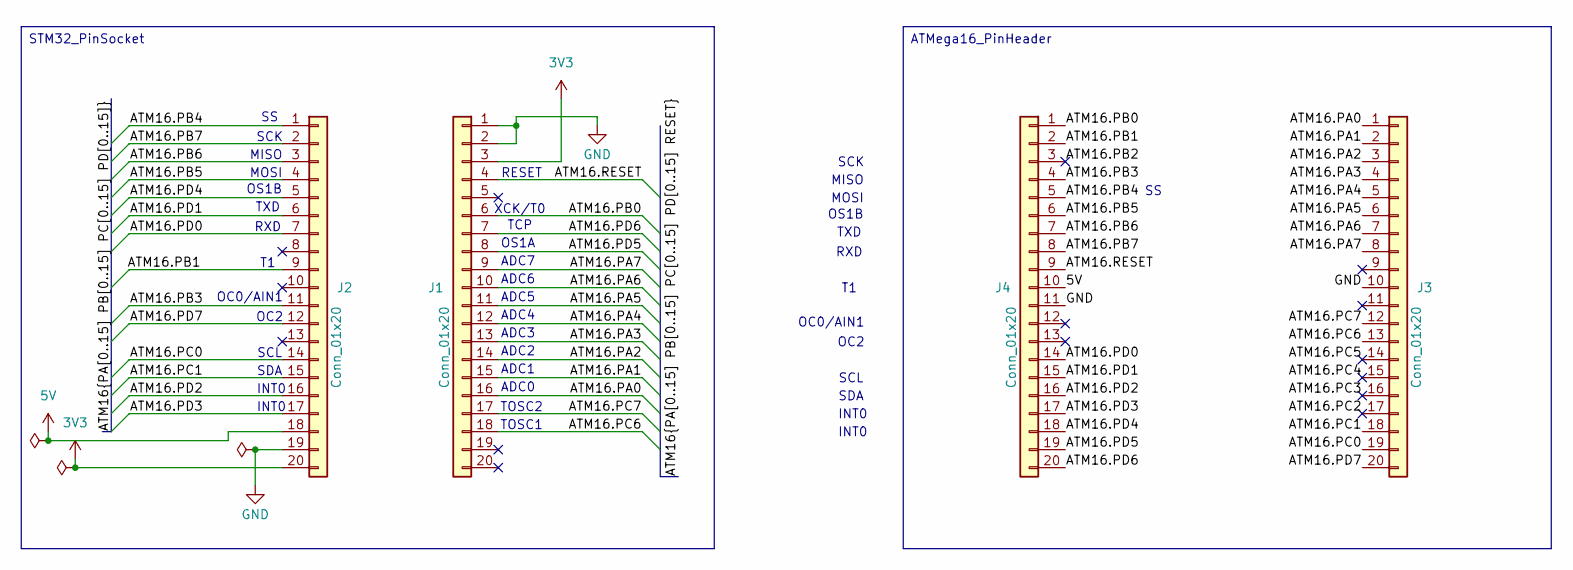
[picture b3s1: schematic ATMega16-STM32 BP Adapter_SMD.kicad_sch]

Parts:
J1: Conn_01x20; PinSocket_1x20_P2.54mm_Vertical_SMD_Pin1Right
J2: Conn_01x20; PinSocket_1x20_P2.54mm_Vertical_SMD_Pin1Left
J3: Conn_01x20; PinHeader_1x20_P2.54mm_Vertical_SMD_Pin1Right
J4: Conn_01x20; PinHeader_1x20_P2.54mm_Vertical_SMD_Pin1Left

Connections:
3V3: J1.3, J2.20
5V: J2.18, J4.10
/ATM16.PA0: J1.16, J3.1
/ATM16.PA1: J1.15, J3.2
/ATM16.PA2: J1.14, J3.3
/ATM16.PA3: J1.13, J3.4
/ATM16.PA4: J1.12, J3.5
/ATM16.PA5: J1.11, J3.6
/ATM16.PA6: J1.10, J3.7
/ATM16.PA7: J1.9, J3.8
/ATM16.PB0: J1.6, J4.1
/ATM16.PB1: J2.9, J4.2
/ATM16.PB2: J4.3
/ATM16.PB3: J2.11, J4.4
/ATM16.PB4: J2.1, J4.5
/ATM16.PB5: J2.4, J4.6
/ATM16.PB6: J2.3, J4.7
/ATM16.PB7: J2.2, J4.8
/ATM16.PC0: J2.14, J3.19
/ATM16.PC1: J2.15, J3.18
/ATM16.PC2: J3.17
/ATM16.PC3: J3.16
/ATM16.PC4: J3.15
/ATM16.PC5: J3.14
/ATM16.PC6: J1.18, J3.13
/ATM16.PC7: J1.17, J3.12
/ATM16.PD0: J2.7, J4.14
/ATM16.PD1: J2.6, J4.15
/ATM16.PD2: J2.16, J4.16
/ATM16.PD3: J2.17, J4.17
/ATM16.PD4: J2.5, J4.18
/ATM16.PD5: J1.8, J4.19
/ATM16.PD6: J1.7, J4.20
/ATM16.PD7: J2.12, J3.20
/ATM16.RESET: J1.4, J4.9
GND: J1.1, J1.2, J2.19, J3.10, J4.11

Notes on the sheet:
OC2
INT0
SCK
RXD
ADC7
RESET
OC0/AIN1
SDA
ADC1
ADC2
SCL
MOSI
TXD
TOSC2
ADC4
OS1A
OS1B
TOSC1
TCP
XCK/T0
MISO
ADC6
ADC5
ADC3
ADC0
ATMega16_PinHeader
STM32_PinSocket

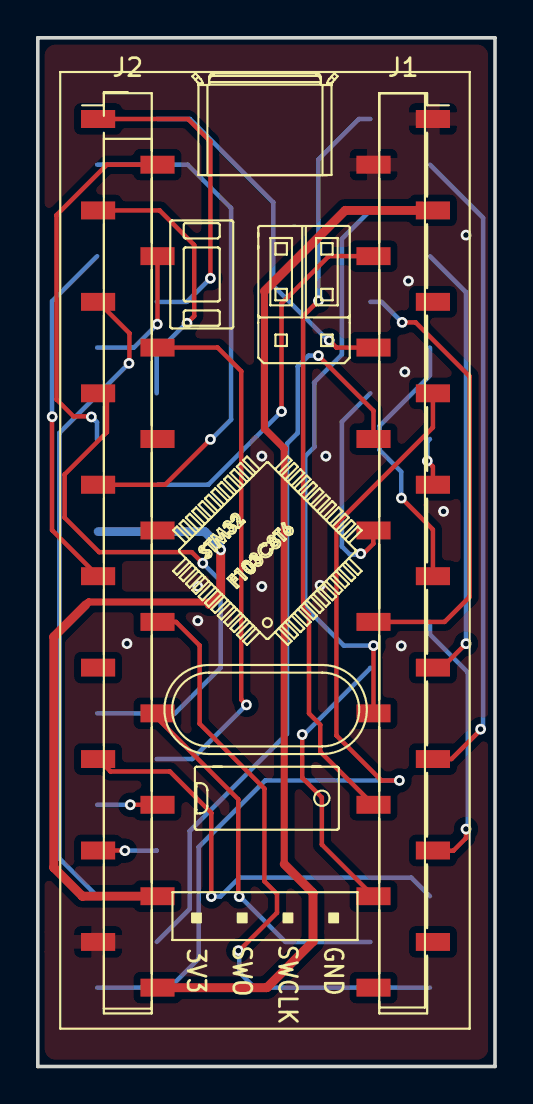
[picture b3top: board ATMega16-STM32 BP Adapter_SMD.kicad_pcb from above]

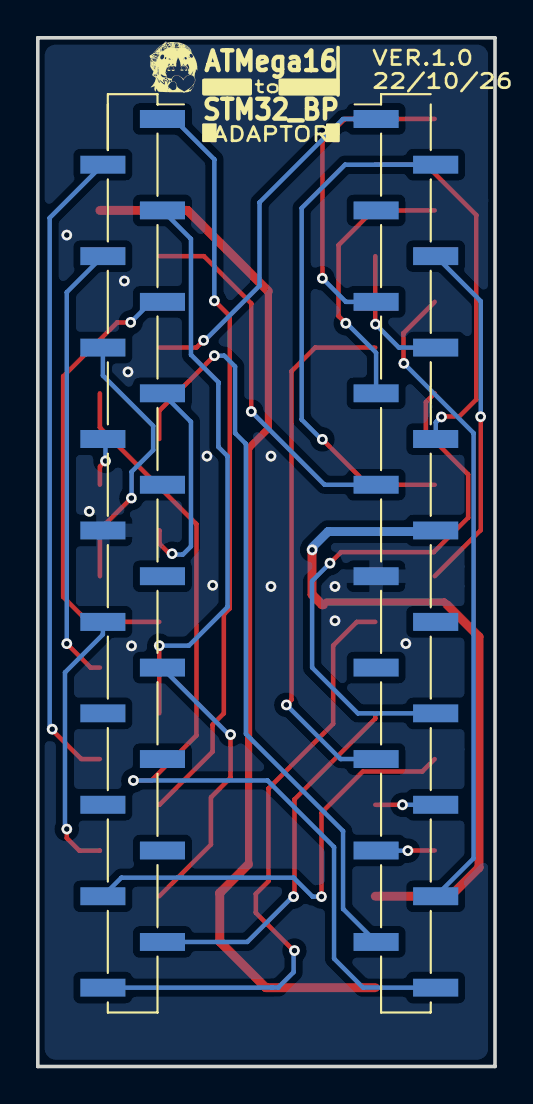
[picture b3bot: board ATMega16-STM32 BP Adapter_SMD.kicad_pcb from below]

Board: 2 copper layers, 25.4 x 57.1 mm, 5 parts (2 on the bottom side), 31 nets.

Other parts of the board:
U2: YAAJ_BluePill_Part_Like; BLUEPILL_SILKSCREEN

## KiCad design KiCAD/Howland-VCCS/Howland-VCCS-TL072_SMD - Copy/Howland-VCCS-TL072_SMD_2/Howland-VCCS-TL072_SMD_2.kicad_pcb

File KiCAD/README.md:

<table align="center">
  <tr>
    <td align="center" valign="middle" width="33%">
      
    </td>
    <td align="center" valign="middle" width="33%">
      
    </td>
    <td align="center" valign="middle" width="33%">
      
    </td>
  </tr>
</table>
<p align="center"><sub>STM32 Blue Pill / Black Pill reference · Arm Cortex core depends on the exact MCU variant</sub></p>

# KiCad Projects

Folder ini menampung schematic, PCB layout, library komponen, dan paket manufaktur dari proyek instrumentasi selama magang.

## Proyek

| Proyek | Fungsi | Status file manufaktur | Area outline PCB |
| --- | --- | --- | ---: |
| [ATmega16–STM32 Adapter (SMD)](ATMega16-STM32%20BP%20Adapter/ATMega16-STM32%20BP%20Adapter_SMD/README.md) | Breakout dan routing pin ATmega16 ke header STM32 | Gerber + drill tersedia | **1,450.75 mm² / 14.5075 cm²** |
| [Howland VCCS TL072 (THT)](Howland-VCCS/Howland-VCCS-TL072/README.md) | Voltage-controlled current source berbasis TL072 | Gerber + drill tersedia | **3,506.24 mm² / 35.0624 cm²** |
| [Howland VCCS TL072 (SMD/hybrid)](Howland-VCCS/Howland-VCCS-TL072_SMD/Howland-VCCS-TL072_SMD/README.md) | Varian Howland dengan resistor SMD dan IC/op-amp THT | Gerber + drill tersedia | **618.85 mm² / 6.1885 cm²** |
| [Impedance Meter Main Board](Impedance-meter2D_Main%20Board/README.md) | Workspace main board impedance meter | File manufaktur belum tersedia di folder | Belum dihitung |
| [Part Libraries](Part%20Lib/README.md) | Symbol, footprint, dan model 3D | Library | — |
| [Raspberry Pi Zero Dev Board](RaspiZeroDevBoard/README.md) | Carrier board Raspberry Pi Zero dengan ADC eksternal, RTC, interface serial, RS-485, LCD, dan rail daya | PCB tersedia; Gerber belum ada | **19,581.96 mm² / 195.8196 cm²** |
| [VCCS 2 Buffer](Howland-VCCS/VCCS%202%20Buffer/README.md) | Workspace schematic buffer berbasis AD826ANZ dan TL082 | PCB masih stub; Gerber/area belum tersedia | Belum dihitung |

### Area board yang sudah dihitung

Dimensi diambil dari geometri `Edge.Cuts` pada file PCB dan dicocokkan dengan layer Gerber profile. Ketiga outline berbentuk persegi panjang dengan empat sudut membulat. Area dihitung sebagai:

`A = (W × H) − (4 − π)r²`

dengan `W` dan `H` sebagai ukuran bounding rectangle dan `r` sebagai radius sudut. Nilai ini adalah luas bidang outline PCB, bukan luas komponen atau bounding box tanpa koreksi sudut.

## Workflow manufaktur KiCad

1. Buka file `.kicad_pro` dari folder proyek.
2. Validasi schematic, footprint, nomor pad, konektor, dan net.
3. Jalankan ERC untuk schematic dan DRC untuk PCB.
4. Plot layer Gerber yang diperlukan dan generate file drill PTH/NPTH.
5. Periksa file `Edge_Cuts.gbr`, `*.gbrjob`, dan arsip ZIP sebelum dikirim ke manufaktur.

Paket Gerber yang tersedia ditautkan dari README masing-masing proyek. Jangan menggunakan file dari folder atau revisi berbeda sebagai satu paket produksi.

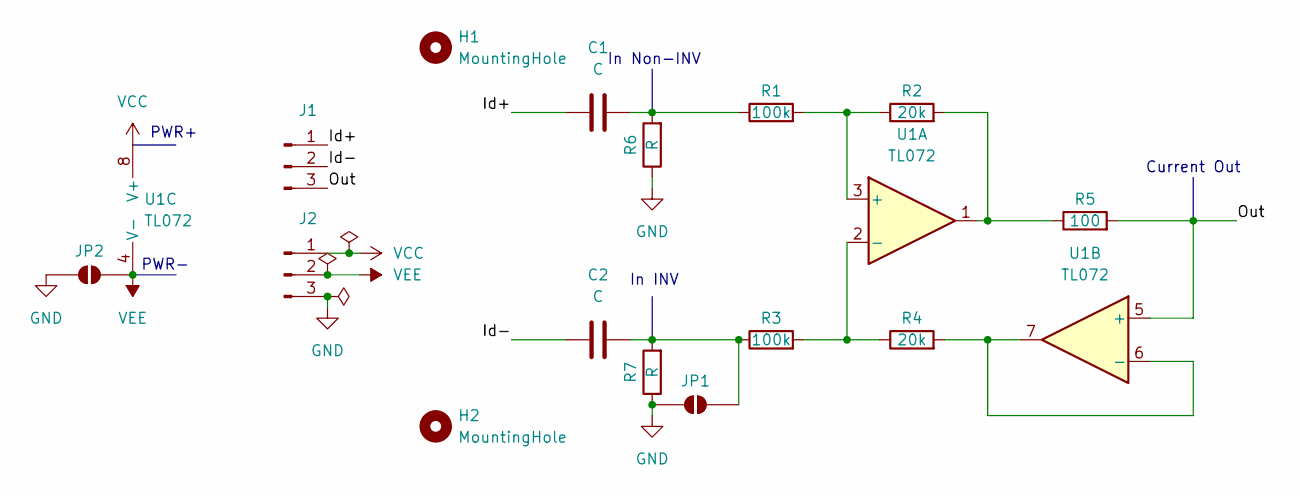
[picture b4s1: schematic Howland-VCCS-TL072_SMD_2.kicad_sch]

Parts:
C1, C2: C; C_0805_2012Metric
H1, H2: MountingHole; MountingHole_2.2mm_M2
J1, J2: Conn_01x03_Pin; PinHeader_1x03_P2.54mm_Vertical
JP1, JP2: SolderJumper_2_Open; SolderJumper-2_P1.3mm_Open_RoundedPad1.0x1.5mm
R1, R3: 100k; R_0805_2012Metric
R2, R4: 20k; R_0805_2012Metric
R5: 100; R_0805_2012Metric
R6, R7: R; R_0805_2012Metric
U1: TL072; DIP-8_W7.62mm

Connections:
/Id+: C1.1, J1.1
/Id-: C2.1, J1.2
/Out: J1.3, R5.2, U1.5 (+)
GND: J2.3, JP1.1 (A), JP2.1 (A), R6.1, R7.1
unnamed: C1.2, R1.1, R6.2
unnamed: C2.2, JP1.2 (B), R3.1, R7.2
unnamed: R2.2, R5.1, U1.1
unnamed: R1.2, R2.1, U1.3 (+)
unnamed: R3.2, R4.1, U1.2 (-)
unnamed: R4.2, U1.6 (-), U1.7
VCC: J2.1, U1.8 (V+)
VEE: J2.2, JP2.2 (B), U1.4 (V-)

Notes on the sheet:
In INV
In Non-INV
PWR-
Current Out
PWR+

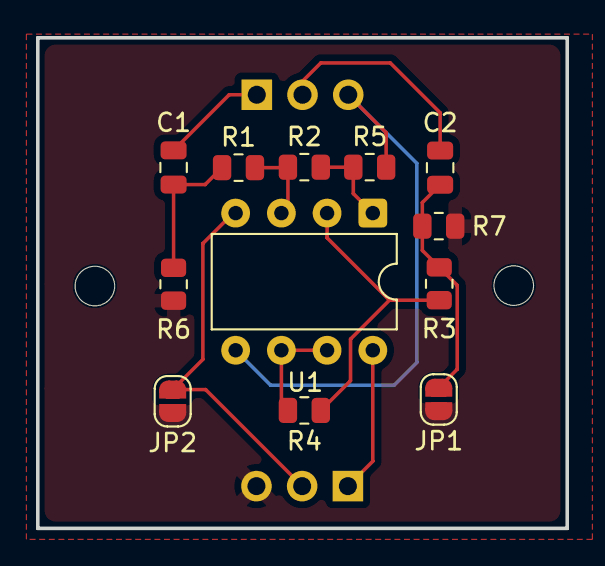
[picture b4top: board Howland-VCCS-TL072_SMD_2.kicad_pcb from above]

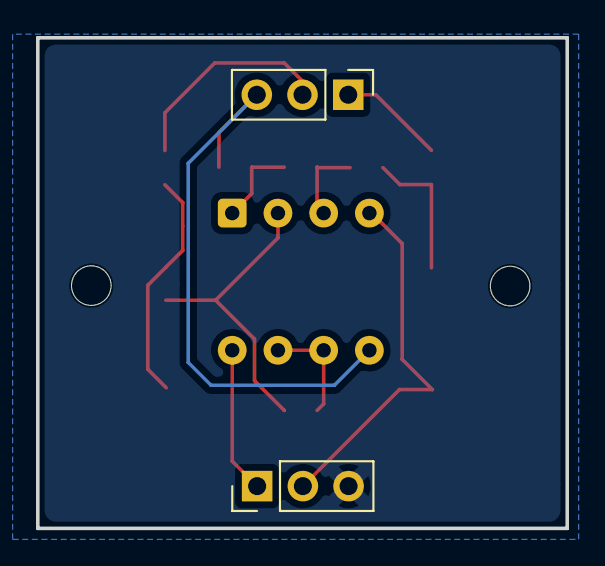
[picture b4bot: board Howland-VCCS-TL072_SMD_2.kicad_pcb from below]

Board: 2 copper layers, 29.4 x 27.3 mm, 16 parts (2 on the bottom side), 12 nets.
